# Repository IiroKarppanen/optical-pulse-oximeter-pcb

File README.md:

# Optical Pulseoximeter

## Board Features
- ESP32-S3-MINI-1-N8 chip to process photodiode signal and interface with LCD display
- Filter and amplifier circuit for photodiode signal
- LED driver enables precise LED switching which can be used for ambient light cancellation

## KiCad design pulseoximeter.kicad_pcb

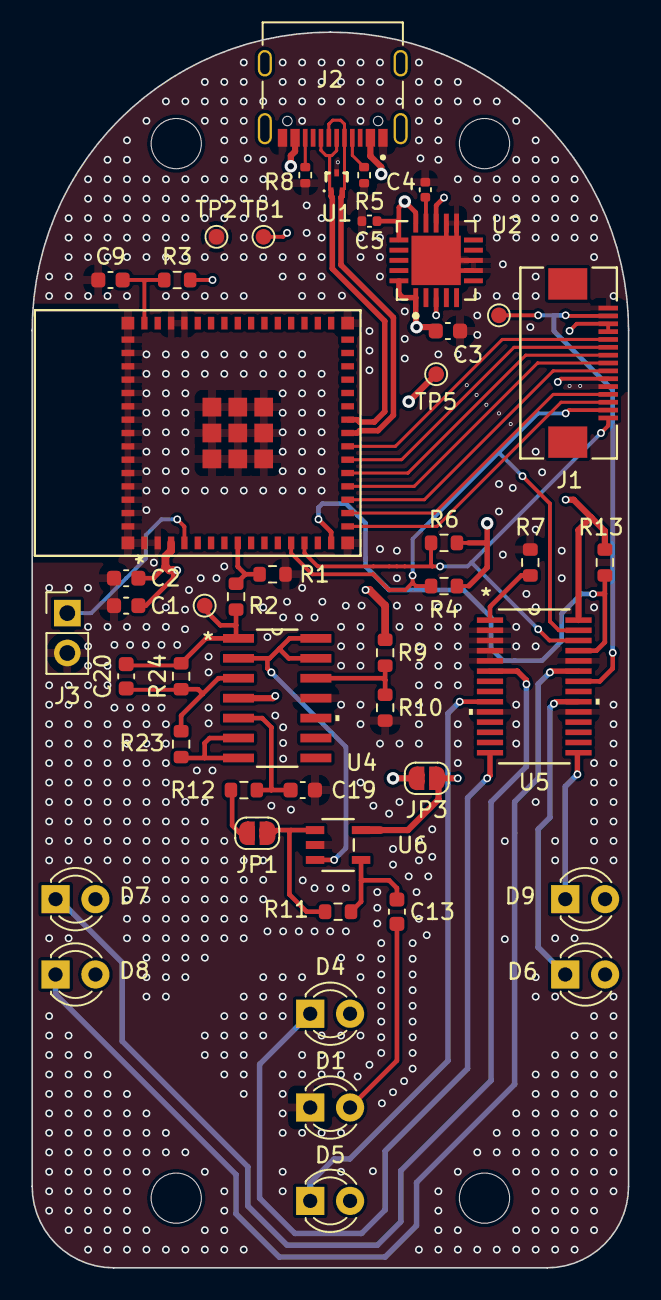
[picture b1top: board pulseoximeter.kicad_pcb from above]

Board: 4 copper layers, 38.0 x 78.7 mm, 47 parts (0 on the bottom side), 40 nets.

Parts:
C1: 10uF; C_0603_1608Metric
C2, C9: 0.1uF; C_0603_1608Metric
C3: 47uF; C_0603_1608Metric
C4: 1uF; C_0402_1005Metric
C5: 10uF; C_0402_1005Metric
C13: 0.22uF; C_0603_1608Metric
C19, C20: 22uF; C_0603_1608Metric
D1: D_Photo; LED_D3.0mm
D4, D5, D6, D7, D8, D9: LED; LED_D3.0mm
J1: X05A20L15T; CONN_X05A20L15T_XKB
J2: TYPE-C-31-M-12
J3: Conn_01x02; PinHeader_1x02_P2.54mm_Vertical
JP1, JP3: SolderJumper_2_Bridged; SolderJumper-2_P1.3mm_Open_RoundedPad1.0x1.5mm
R1, R9, R10: 100k; R_0603_1608Metric
R2: 50k; R_0603_1608Metric
R3, R13: 10k; R_0603_1608Metric
R4, R6: 2k2; R_0603_1608Metric
R5, R8: 5.1k; R_0402_1005Metric
R7: 910; R_0603_1608Metric
R11: 5.6M; R_0603_1608Metric
R12: 33k; R_0603_1608Metric
R23: 100R; R_0603_1608Metric
R24: 1.8k; R_0603_1608Metric
TP1, TP2, TP3, TP4, TP5: TestPoint; TestPoint_Pad_D1.0mm
U1: TPD2EUSB30DRTR; DRT0003A
U2: TPS7A4700RGWR; RGW0020A-IPC_A
U3: ESP32-S3-MINI-1-N8; ESP32-S3-MINI-1_EXP
U4: LM324; D14
U5: TLC59116IPWR; PW28
U6: OPA140AIDBVR; DBV5-M

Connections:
+3.3V: C1.1, C2.1, C3.1, J1.3, J1.4, J1.10, R3.1, R4.1, R6.1, R9.1, R13.2, TP5.1, U2.1 (OUT), U2.3 (SENSE_FB), U2.20 (OUT), U3.3 (3V3), U5.28 (VCC)
/DISPLAY_CLK: J1.7, U3.20 (IO16)
/DISPLAY_CS: J1.6, U3.21 (IO17)
/DISPLAY_D/C: J1.5, U3.22 (IO18)
/DISPLAY_RESET: J1.9, U3.18 (IO14)
/DISPLAY_SDI: J1.8, U3.19 (IO15)
/IO0: J3.1, U3.4 (IO0)
/LEDK: J1.2, TP4.1, U5.22 (*OUT14)
/LED_RST: R13.1, U3.15 (IO11), U5.25 (*RESET)
/TP_INT: J1.13, U3.16 (IO12)
/TP_RST: J1.12, U3.17 (IO13)
DN: J2.A7 (DN1), J2.B7 (DN2), U1.2 (D-), U3.23 (IO19)
DP: J2.A6 (DP1), J2.B6 (DP2), U1.1 (D+), U3.24 (IO20)
GND: C1.2, C2.2, C3.2, C4.1, C5.2, C9.2, C19.2, D1.1 (K), J1.1, J1.11, J2.A1_B12 (GND), J2.B1_A12 (GND), J3.2, R1.2, R5.2, R7.1, R8.2, R10.2, TP2.1, U1.3 (GND), U2.7 (GND), U2.8 (1P6V), U2.11 (0P2V), U2.12 (0P1V), U2.21 (Thermal_Pad), U3.1 (GND), U3.2 (GND), U3.42 (GND), U3.43 (GND), U3.46 (GND), U3.47 (GND), U3.48 (GND), U3.49 (GND), U3.50 (GND), U3.51 (GND), U3.52 (GND), U3.53 (GND), U3.54 (GND), U3.55 (GND), U3.56 (GND), U3.57 (GND), U3.58 (GND), U3.59 (GND), U3.60 (GND), U3.61 (GND), U3.62 (GND), U3.63 (GND), U3.64 (GND), U3.65 (GND), U3.66 (GND), U3.67 (GND), U3.68 (GND), U3.69 (GND), U3.70 (GND), U3.71 (GND), U3.72 (GND), U3.73 (GND), U4.11 (V-), U5.2 (A0), U5.3 (A1), U5.4 (A2), U5.5 (A3), U5.10 (GND), U5.19 (GND), U5.24 (GND), U6.2 (V-)
HR_SIGNAL: R1.1, R2.2, U3.8 (IO4)
unnamed: C20.1, R2.1, R24.1, TP3.1, U4.1
unnamed: C13.1, D1.2 (A)
unnamed: D4.1 (K), U5.14 (*OUT7)
unnamed: D5.1 (K), U5.9 (*OUT3)
unnamed: D6.1 (K), U5.20 (*OUT12)
unnamed: D7.1 (K), U5.6 (*OUT0)
unnamed: D8.1 (K), U5.23 (*OUT15)
unnamed: D9.1 (K), U5.15 (*OUT8)
unnamed: J2.A5 (CC1), R5.1
unnamed: J2.B5 (CC2), R8.1
unnamed: JP1.1 (A), R11.1, U6.1 (OUT)
unnamed: JP1.2 (B), R12.2
unnamed: JP3.2 (B), U4.4 (V+)
unnamed: C4.2, U2.14 (NR)
unnamed: C9.1, R3.2, U3.45 (EN)
unnamed: C20.2, R23.1, R24.2, U4.3 (+)
unnamed: C19.1, R12.1, U4.5 (+)
unnamed: R23.2, U4.6 (-), U4.7
unnamed: R9.2, R10.1, U4.12 (+)
unnamed: R7.2, U5.1 (REXT)
unnamed: C13.2, R11.2, U6.4 (IN-)
SCL: J1.15, R6.2, U3.13 (IO9), U5.26 (SCL)
SDA: J1.14, R4.2, U3.12 (IO8), U5.27 (SDA)
VBUS: C5.1, D4.2 (A), D5.2 (A), D6.2 (A), D7.2 (A), D8.2 (A), D9.2 (A), J2.A4_B9 (VBUS), J2.B4_A9 (VBUS), JP3.1 (A), TP1.1, U2.13 (EN), U2.15 (IN), U2.16 (IN), U6.5 (V+)
VCC/2: U4.2 (-), U4.13 (-), U4.14, U6.3 (IN+)

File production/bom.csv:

Designator,Footprint,Quantity,Value,LCSC Part #
C1,0603,1,10uF,
C13,0603,1,0.22uF,
"C19, C20",0603,2,22uF,
"C2, C9",0603,2,0.1uF,
C3,0603,1,47uF,
C4,0402,1,1uF,
C5,0402,1,10uF,
J1,CONN_X05A20L15T_XKB,1,X05A20L15T,
J2,TYPE-C-31-M-12,1,TYPE-C-31-M-12,
"R1, R10, R9",0603,3,100k,
R11,0603,1,5.6M,
R12,0603,1,33k,
"R13, R3",0603,2,10k,
R2,0603,1,50k,
R23,0603,1,100R,
R24,0603,1,1.8k,
"R4, R6",0603,2,2k2,
"R5, R8",0402,2,5.1k,
R7,0603,1,910,
U1,DRT0003A,1,TPD2EUSB30DRTR,
U2,RGW0020A-IPC_A,1,TPS7A4700RGWR,
U3,ESP32-S3-MINI-1_EXP,1,ESP32-S3-MINI-1-N8,
U4,D14,1,LM324,
U5,PW28,1,TLC59116IPWR,
U6,DBV5-M,1,OPA140AIDBVR,

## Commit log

2024-11-07 layout complete
2024-12-02 tuned passive component values
